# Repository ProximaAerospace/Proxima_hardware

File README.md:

# Proxima Hardware
Here you can find all CAD files for Proxima Official Flight Computers

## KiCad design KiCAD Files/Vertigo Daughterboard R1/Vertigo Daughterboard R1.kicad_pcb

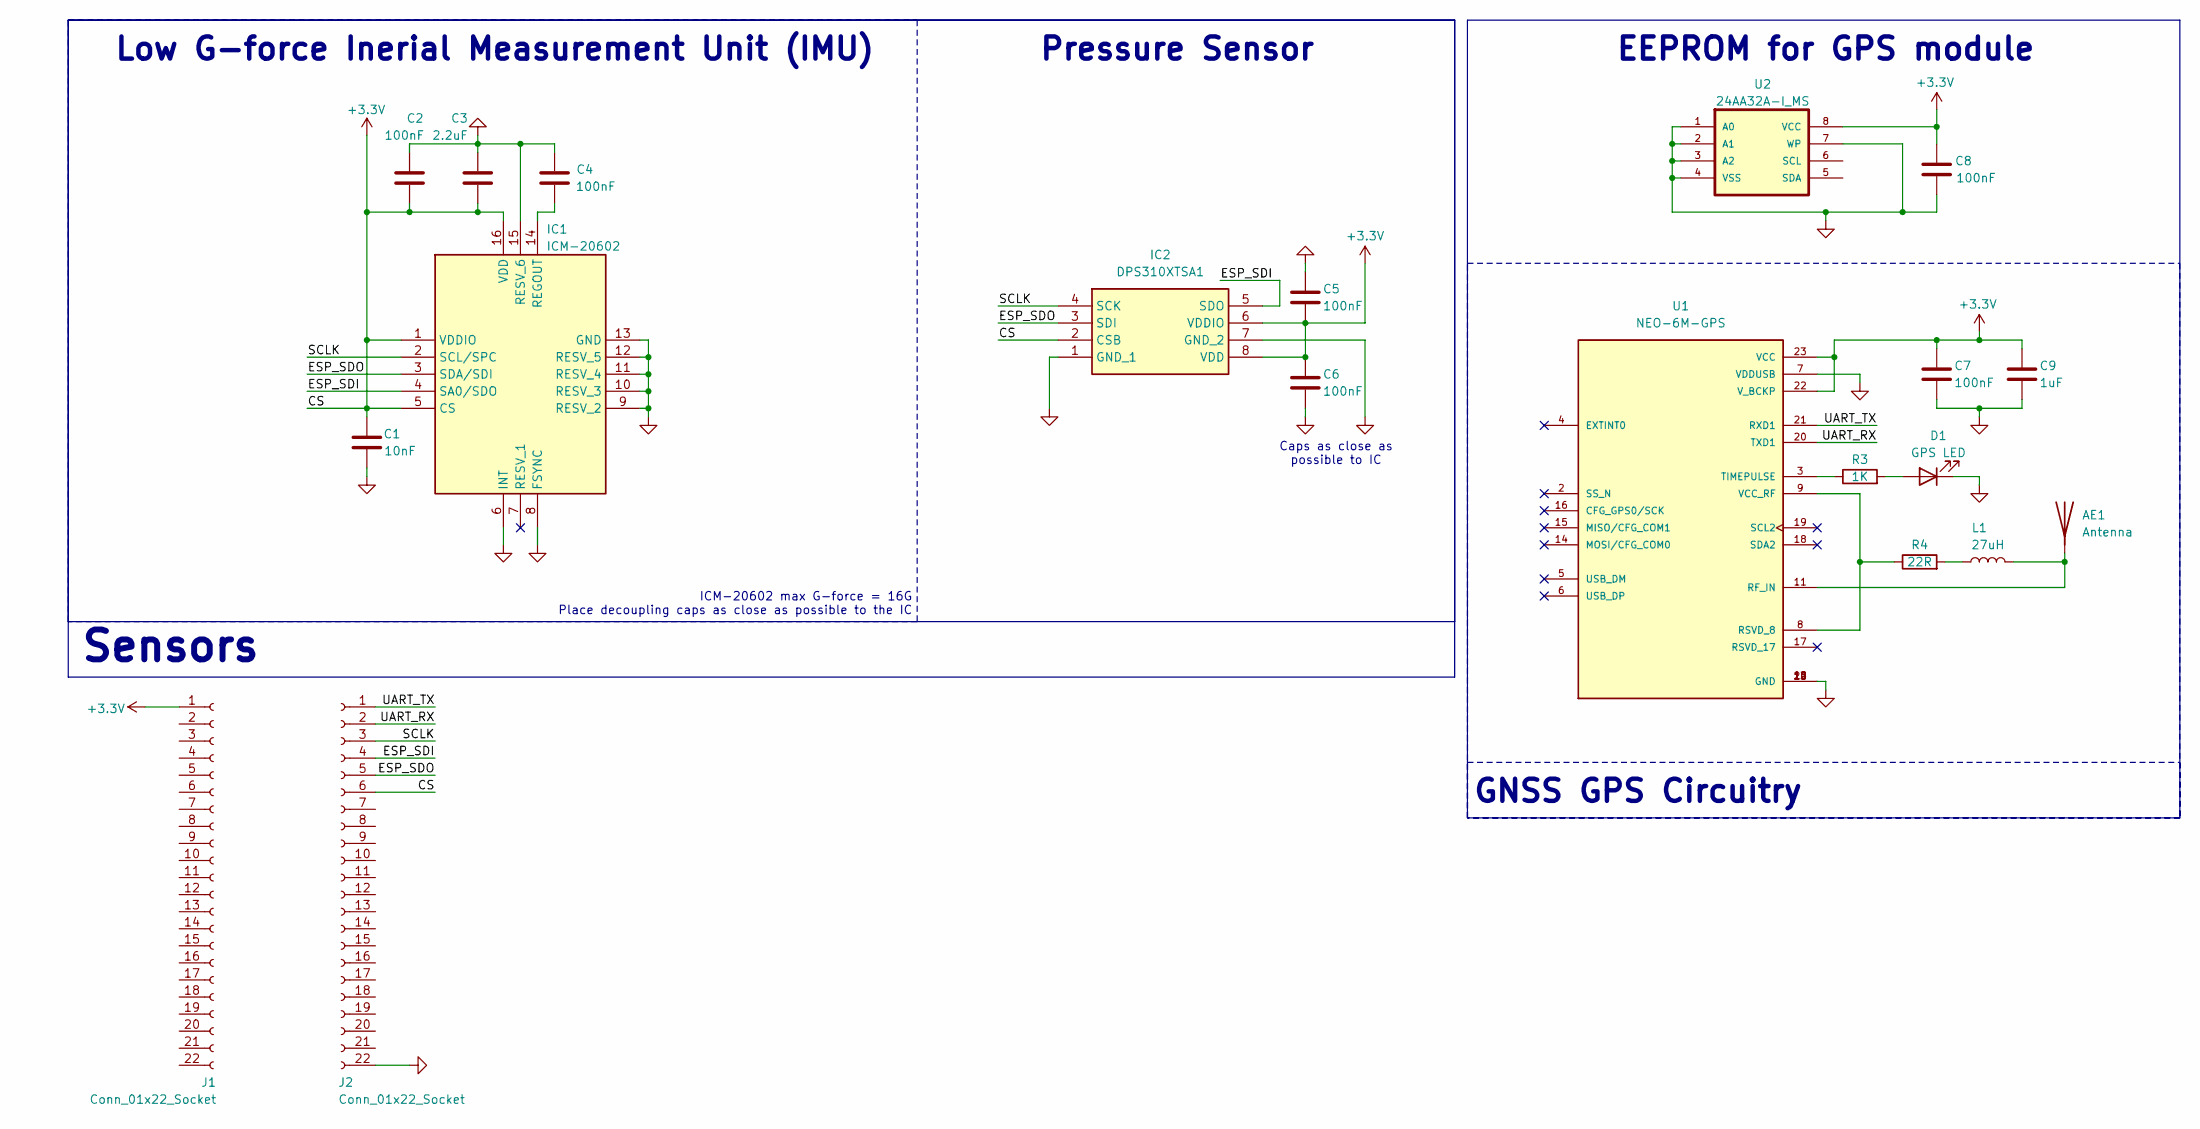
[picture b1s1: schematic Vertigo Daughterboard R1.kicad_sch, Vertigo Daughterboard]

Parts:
AE1: Antenna; U.FL_Hirose_U.FL-R-SMT-1_Vertical
C1: 10nF; C_0603_1608Metric
C2, C4, C5, C6, C7, C8: 100nF; C_0603_1608Metric
C3: 2.2uF; C_0603_1608Metric
C9: 1uF; C_0603_1608Metric
D1: GPS LED; LED_0603_1608Metric_Pad1.05x0.95mm_HandSolder
IC1: ICM-20602; PQFN50P300X300X80-16N; Manufacturer_Part_Number ICM-20602; Mouser Part Number 410-ICM-20602
IC2: DPS310XTSA1; Manufacturer_Part_Number DPS310XTSA1; Mouser Part Number 726-DPS310XTSA1
J1, J2: Conn_01x22_Socket; PinHeader_1x22_P2.54mm_Vertical
L1: 27uH; L_0402_1005Metric
R3: 1K; R_0805_2012Metric
R4: 22R; R_0402_1005Metric
U1: NEO-6M-GPS; XCVR_NEO-6M-GPS; PARTREV R15
U2: 24AA32A-I_MS; SOP65P490X110-8N

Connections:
+3.3V: C1.2, C2.2, C3.2, C5.2, C6.1, C7.1, C8.2, C9.1, IC1.1 (VDDIO), IC1.5 (CS), IC1.16 (VDD), IC2.2 (CSB), IC2.6 (VDDIO), IC2.8 (VDD), J1.1, J2.6, U1.22 (V_BCKP), U1.23 (VCC), U2.8 (VCC)
/ESP_SDI: IC1.4 (SA0/SDO), IC2.5 (SDO), J2.4
/ESP_SDO: IC1.3 (SDA/SDI), IC2.3 (SDI), J2.5
/SCLK: IC1.2 (SCL/SPC), IC2.4 (SCK), J2.3
/UART_RX: J2.2, U1.20 (TXD1)
/UART_TX: J2.1, U1.21 (RXD1)
GND: C1.1, C2.1, C3.1, C4.2, C5.1, C6.2, C7.2, C8.1, C9.2, D1.1 (K), IC1.6 (INT), IC1.8 (FSYNC), IC1.9 (RESV_2), IC1.10 (RESV_3), IC1.11 (RESV_4), IC1.12 (RESV_5), IC1.13 (GND), IC1.15 (RESV_6), IC2.1 (GND_1), IC2.7 (GND_2), J2.22, U1.7 (VDDUSB), U1.10 (GND), U1.12 (GND), U1.13 (GND), U1.24 (GND), U2.1 (A0), U2.2 (A1), U2.3 (A2), U2.4 (VSS), U2.7 (WP)
unnamed: AE1.1 (A), L1.2, U1.11 (RF_IN)
unnamed: D1.2 (A), R3.2
unnamed: C4.1, IC1.14 (REGOUT)
unnamed: L1.1, R4.2
unnamed: R4.1, U1.8 (RSVD_8), U1.9 (VCC_RF)
unnamed: R3.1, U1.3 (TIMEPULSE)

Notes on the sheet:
Caps as close as possible to IC
EEPROM for GPS module
GNSS GPS Circuitry
Sensors
ICM-20602 max G-force = 16G Place decoupling caps as close as possible to the IC
Low G-force Inerial Measurement Unit (IMU)
Pressure Sensor

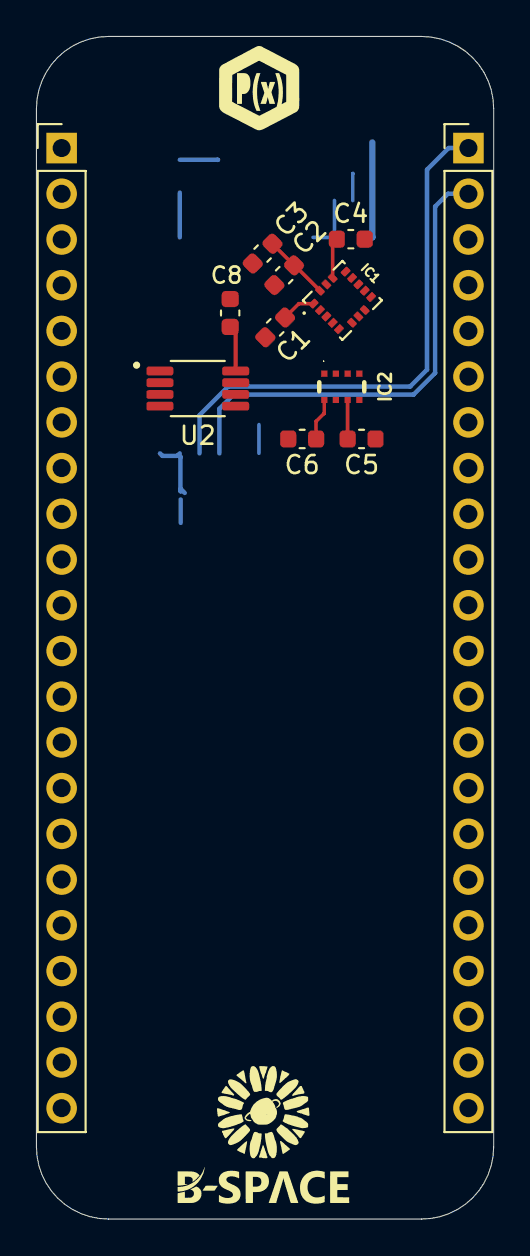
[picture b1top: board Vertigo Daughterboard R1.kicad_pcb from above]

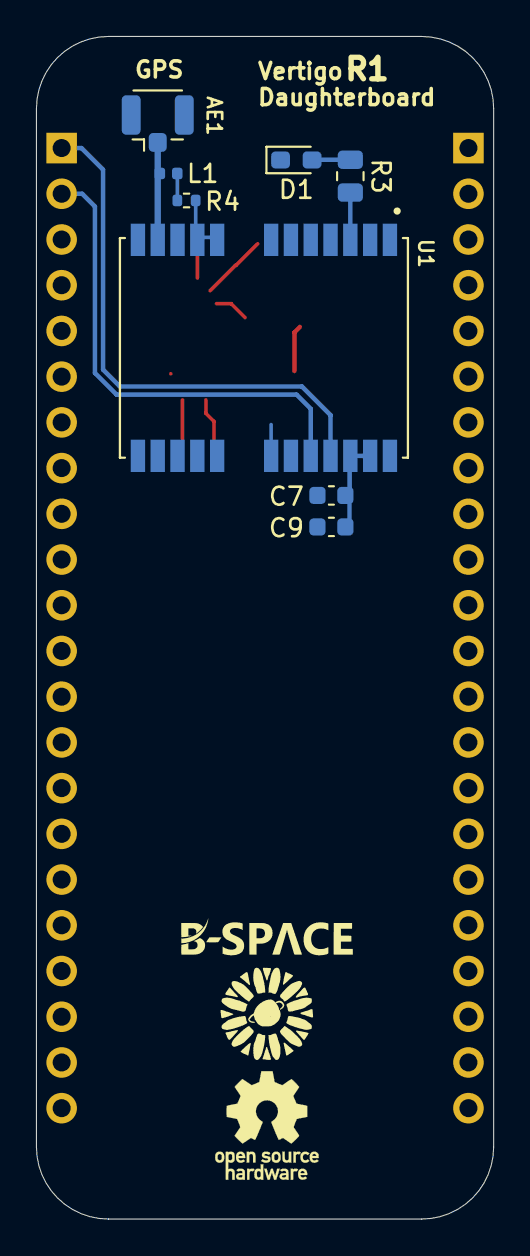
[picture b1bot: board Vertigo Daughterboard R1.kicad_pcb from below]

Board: 4 copper layers, 25.4 x 65.7 mm, 20 parts (8 on the bottom side), 13 nets.

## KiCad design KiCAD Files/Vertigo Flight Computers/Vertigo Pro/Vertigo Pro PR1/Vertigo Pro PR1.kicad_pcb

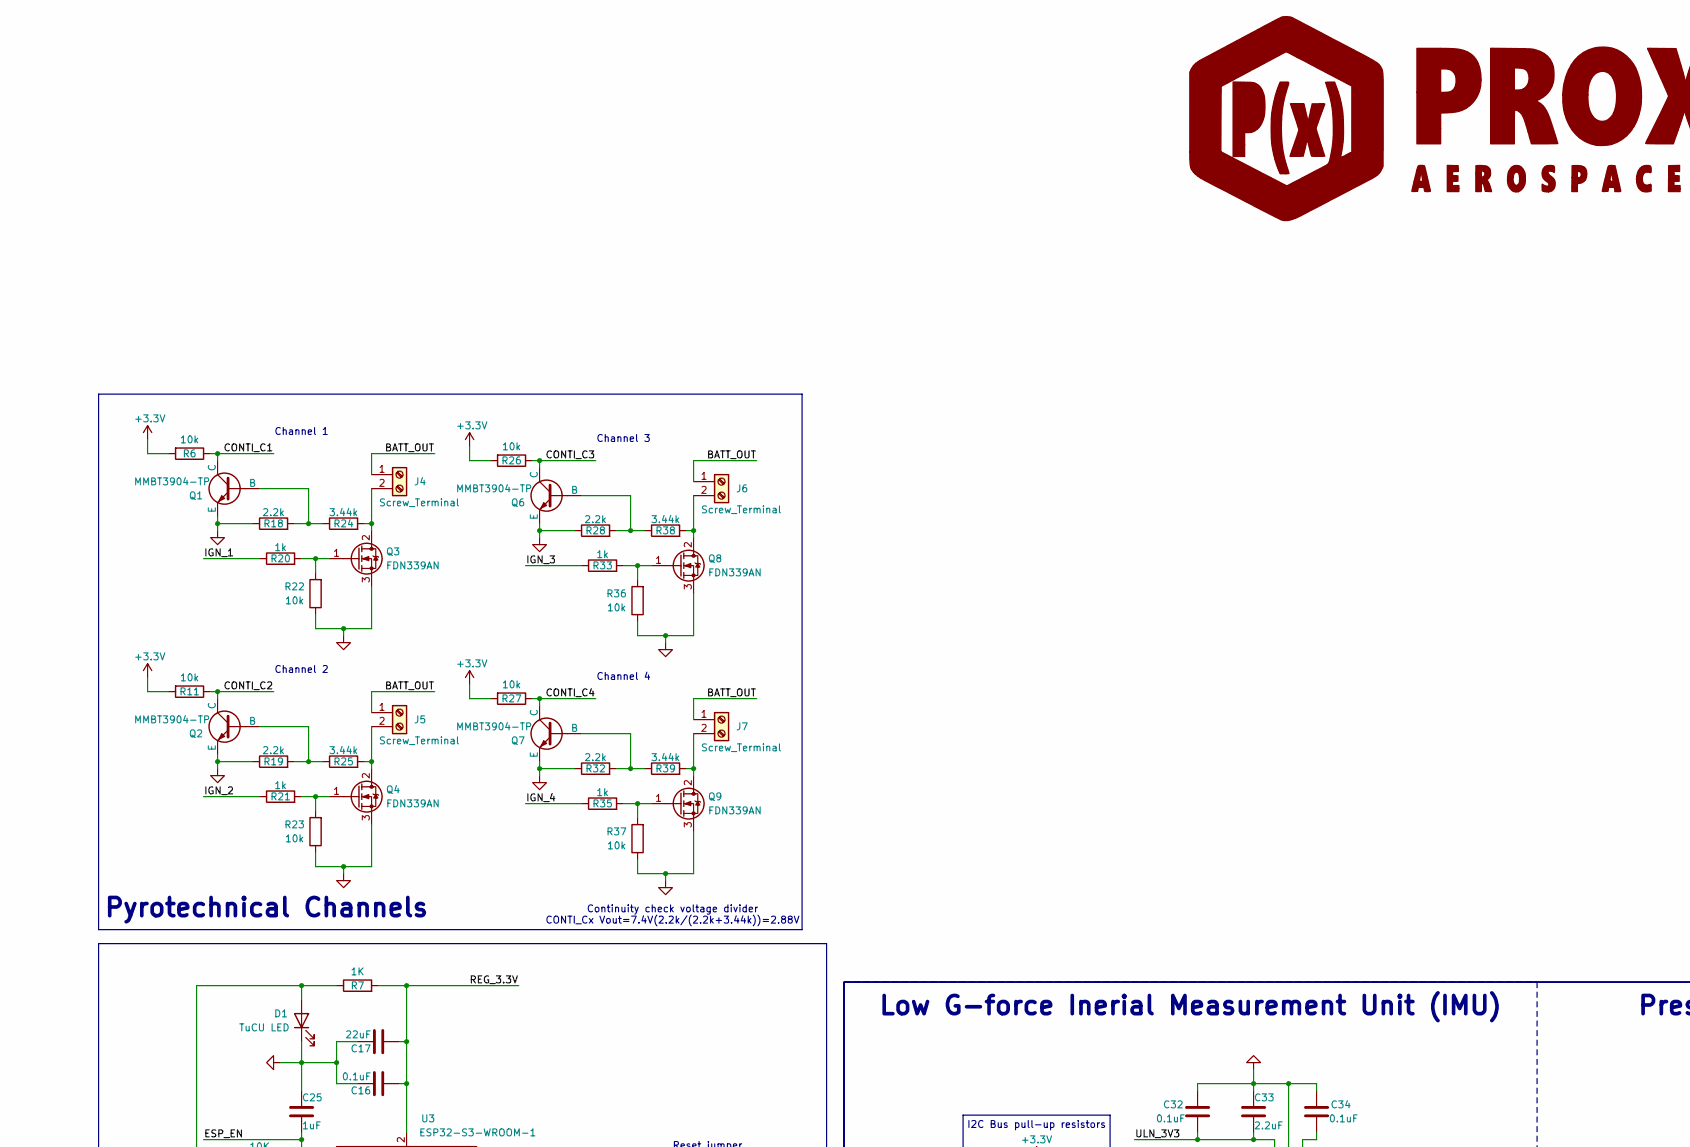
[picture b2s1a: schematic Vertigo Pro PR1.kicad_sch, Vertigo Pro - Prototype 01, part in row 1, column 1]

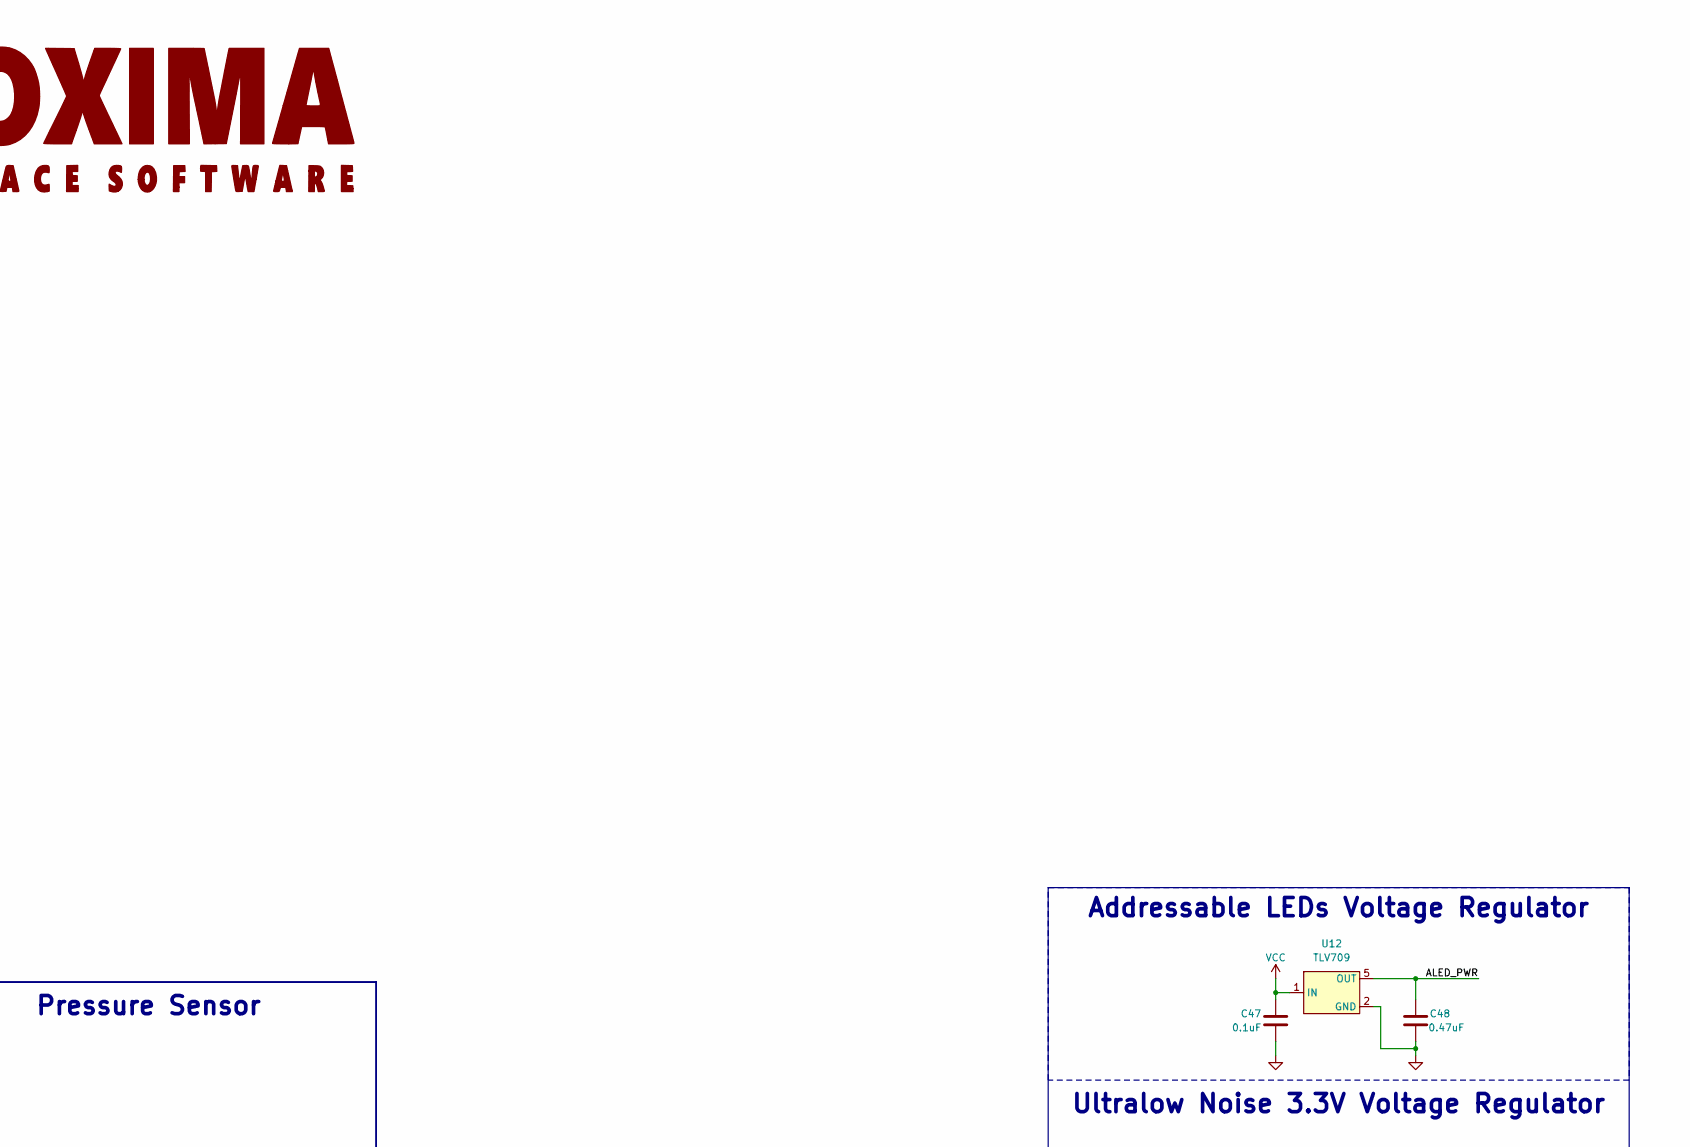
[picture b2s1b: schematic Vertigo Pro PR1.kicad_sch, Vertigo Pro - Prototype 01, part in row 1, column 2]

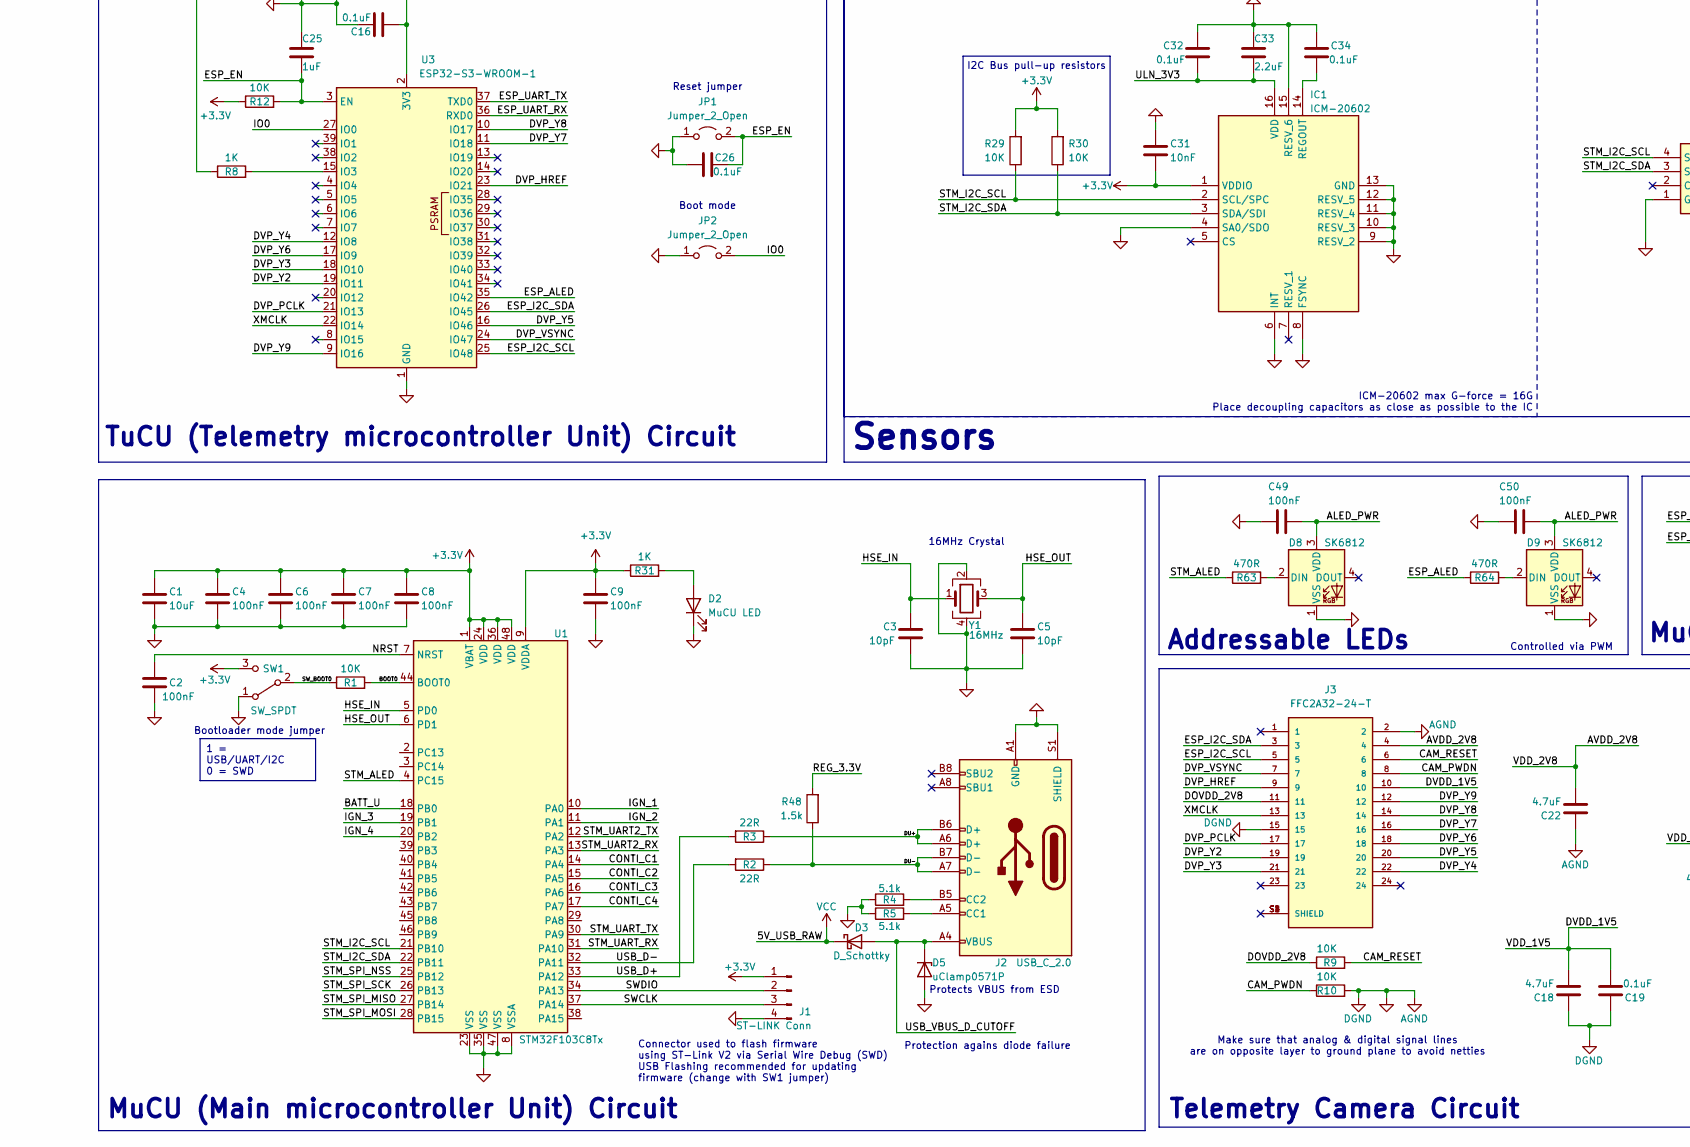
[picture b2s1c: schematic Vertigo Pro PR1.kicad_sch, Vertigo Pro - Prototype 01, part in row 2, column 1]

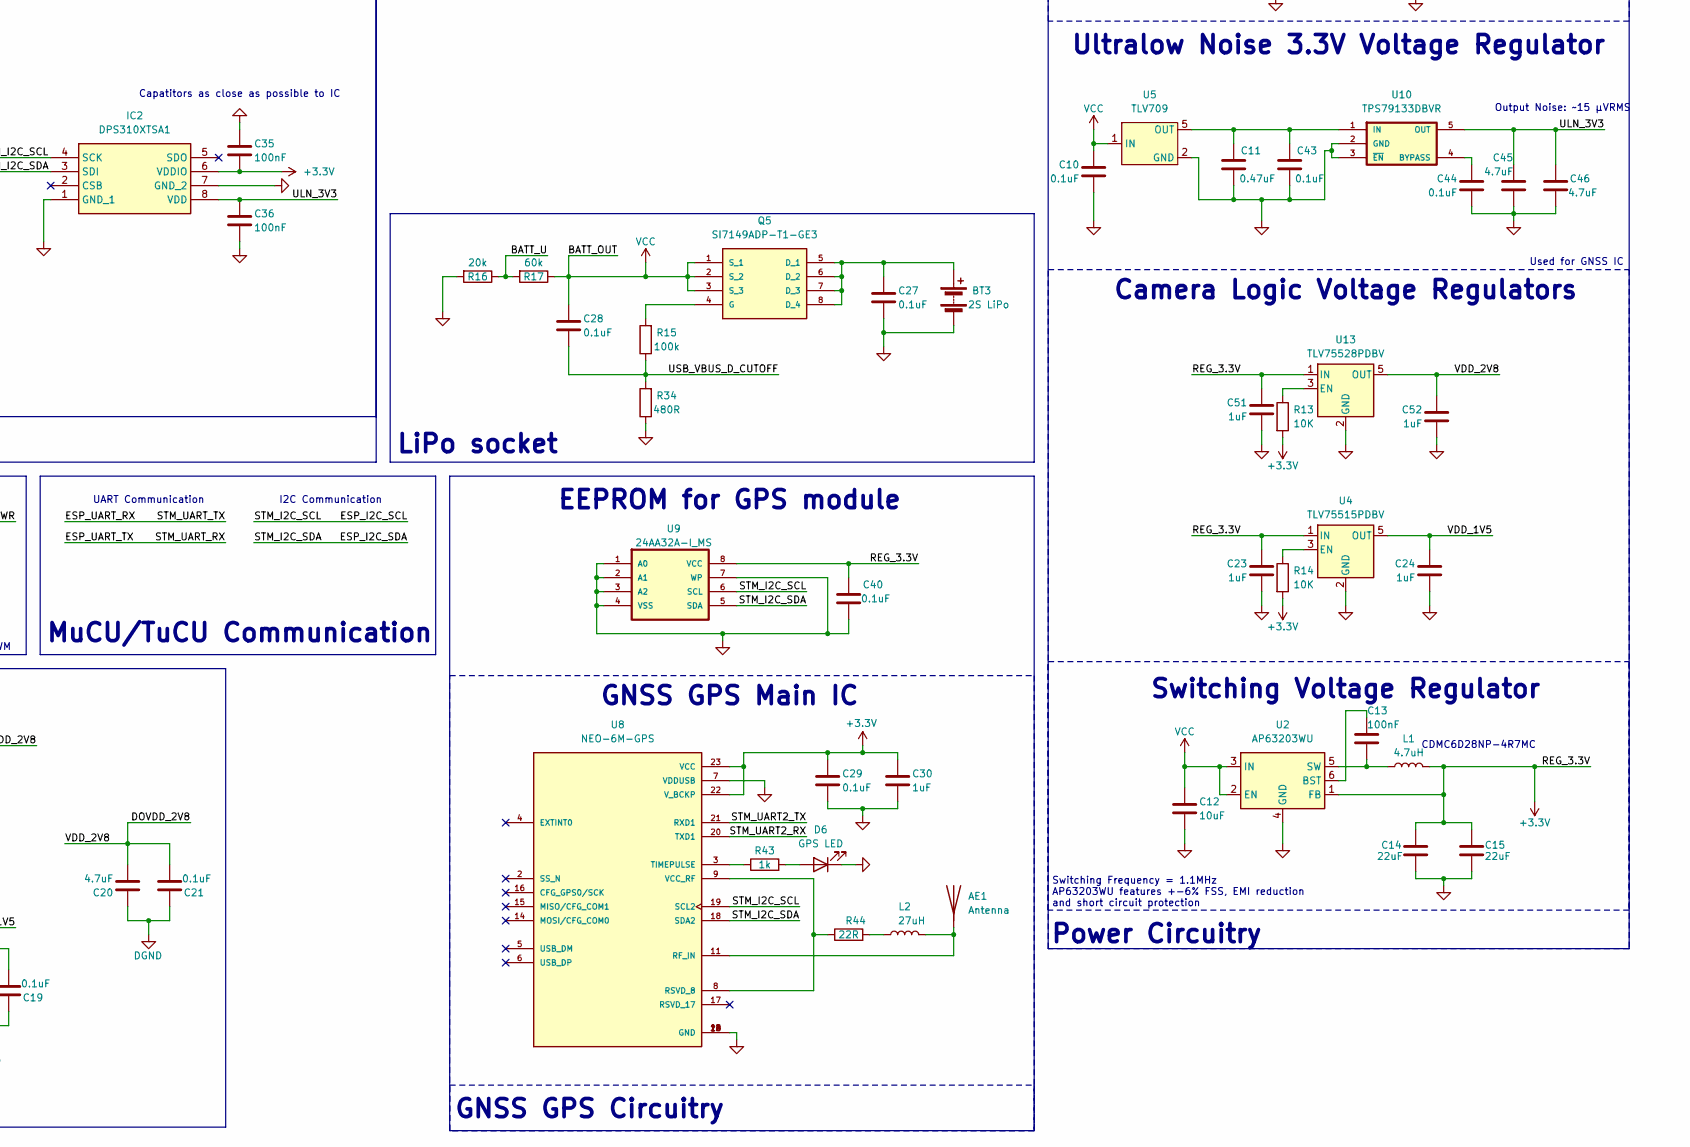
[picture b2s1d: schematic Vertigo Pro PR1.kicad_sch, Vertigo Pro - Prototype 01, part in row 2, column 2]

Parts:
AE1: Antenna; U.FL_Hirose_U.FL-R-SMT-1_Vertical
BT3: 2S LiPo; AMASS_XT30PW-F_1x02_P2.50mm_Horizontal
C1: 10uF; C_0603_1608Metric
C2, C4, C6, C7, C8, C9, C35, C36, C49, C50: 100nF; C_0603_1608Metric
C3, C5: 10pF; C_0603_1608Metric
C10, C16, C19, C21, C26, C32, C34, C40, C43, C44, C47: 0.1uF; C_0603_1608Metric
C11, C48: 0.47uF; C_0603_1608Metric
C12: 10uF; C_0603_1608Metric_Pad1.08x0.95mm_HandSolder
C13: 100nF; C_0603_1608Metric_Pad1.08x0.95mm_HandSolder
C14, C15, C17: 22uF; C_0603_1608Metric_Pad1.08x0.95mm_HandSolder
C18, C20, C45, C46: 4.7uF; C_0603_1608Metric_Pad1.08x0.95mm_HandSolder
C22: 4.7uF; C_0603_1608Metric
C23, C24, C25, C30, C51, C52: 1uF; C_0603_1608Metric_Pad1.08x0.95mm_HandSolder
C27, C28, C29: 0.1uF; C_0603_1608Metric_Pad1.08x0.95mm_HandSolder
C31: 10nF; C_0603_1608Metric
C33: 2.2uF; C_0603_1608Metric_Pad1.08x0.95mm_HandSolder
D1: TuCU LED; LED_0603_1608Metric_Pad1.05x0.95mm_HandSolder
D2: MuCU LED; LED_0603_1608Metric_Pad1.05x0.95mm_HandSolder
D3: D_Schottky; D_0603_1608Metric_Pad1.05x0.95mm_HandSolder
D5: uClamp0571P; Nexperia_DSN1608-2_1.6x0.8mm
D6: GPS LED; LED_0603_1608Metric_Pad1.05x0.95mm_HandSolder
D8, D9: SK6812; LED_SK6812_PLCC4_5.0x5.0mm_P3.2mm
IC1: ICM-20602; PQFN50P300X300X80-16N; Manufacturer_Part_Number ICM-20602; Mouser Part Number 410-ICM-20602
IC2: DPS310XTSA1; Manufacturer_Part_Number DPS310XTSA1; Mouser Part Number 726-DPS310XTSA1
J1: ST-LINK Conn; PinSocket_1x04_P1.27mm_Vertical
J2: USB_C_2.0; USB_C_Receptacle_HRO_TYPE-C-31-M-12
J3: FFC2A32-24-T; GCT_FFC2A32-24-T; PARTREV 0.1
J4, J5, J6, J7: Screw_Terminal; TerminalBlock_4Ucon_1x02_P3.50mm_Horizontal
JP1, JP2: Jumper_2_Open; SolderJumper-2_P1.3mm_Open_TrianglePad1.0x1.5mm
L1: 4.7uH; CDMC6D28NP-4R7MC
L2: 27uH; L_0402_1005Metric
Q1, Q2, Q6, Q7: MMBT3904-TP; SOT-23
Q3, Q4, Q8, Q9: FDN339AN; SOT-23
Q5: SI7149ADP-T1-GE3; POWERPAKSO-8; MOUSER_PART_NUMBER 78-SI7149ADP-T1-GE3
R1: 10K; R_0603_1608Metric
R2, R3: 22R; R_0603_1608Metric
R4, R5: 5.1k; R_0805_2012Metric_Pad1.20x1.40mm_HandSolder
R6, R11, R22, R23, R26, R27, R36, R37: 10k; R_0805_2012Metric_Pad1.20x1.40mm_HandSolder
R7, R8, R31: 1K; R_0805_2012Metric_Pad1.20x1.40mm_HandSolder
R9, R10, R12, R13, R14, R29, R30: 10K; R_0805_2012Metric_Pad1.20x1.40mm_HandSolder
R15: 100k; R_0805_2012Metric_Pad1.20x1.40mm_HandSolder
R16: 20k; R_0805_2012Metric_Pad1.20x1.40mm_HandSolder
R17: 60k; R_0805_2012Metric_Pad1.20x1.40mm_HandSolder
R18, R19, R28, R32: 2.2k; R_0805_2012Metric_Pad1.20x1.40mm_HandSolder
R20, R21, R33, R35, R43: 1k; R_0805_2012Metric_Pad1.20x1.40mm_HandSolder
R24, R25, R38, R39: 3.44k; R_0805_2012Metric_Pad1.20x1.40mm_HandSolder
R34: 480R; R_0805_2012Metric_Pad1.20x1.40mm_HandSolder
R44: 22R; R_0402_1005Metric
R48: 1.5k; R_0603_1608Metric
R63, R64: 470R; R_1206_3216Metric
SW1: SW_SPDT; SolderJumper-3_P2.0mm_Open_TrianglePad1.0x1.5mm_NumberLabels
U1: STM32F103C8Tx; LQFP-48_7x7mm_P0.5mm
U2: AP63203WU; TSOT-23-6
U3: ESP32-S3-WROOM-1
U4: TLV75515PDBV; SOT-23-5
U5, U12: TLV709; SOT95P280X145-5N
U8: NEO-6M-GPS; XCVR_NEO-6M-GPS; PARTREV R15
U9: 24AA32A-I_MS; SOP65P490X110-8N
U10: TPS79133DBVR; SOT95P280X145-5N
U13: TLV75528PDBV; SOT-23-5
Y1: 16MHz; XTAL_TSX-3225_16.0000MF09Z-AC6

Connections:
+3.3V: C1.1, C4.1, C6.1, C7.1, C8.1, C9.1, C14.1, C15.1, C16.2, C17.2, C23.2, C29.1, C30.1, C31.2, C35.2, C40.2, C51.2, IC1.1 (VDDIO), IC2.6 (VDDIO), J1.1, L1.2, R6.2, R7.2, R11.2, R12.1, R13.2, R14.2, R26.2, R27.2, R29.2, R30.2, R31.1, R48.2, SW1.3 (C), U1.1 (VBAT), U1.9 (VDDA), U1.24 (VDD), U1.36 (VDD), U1.48 (VDD), U2.1 (FB), U3.2 (3V3), U4.1 (IN), U8.22 (V_BCKP), U8.23 (VCC), U9.8 (VCC), U13.1 (IN); also elsewhere on the board
/ALED_PWR: C48.2, C49.1, C50.1, D8.3 (VDD), D9.3 (VDD), U12.5 (OUT)
/AVDD_2V8: C20.2, C21.2, C22.2, C52.2, J3.4, J3.11, R9.1, U13.5 (OUT)
/BATT_U: R16.1, R17.2, U1.18 (PB0)
/BOOT0: R1.2, U1.44 (BOOT0)
/CAM_PWDN: J3.8, R10.1
/CAM_RESET: J3.6, R9.2
/CONTI_C1: Q1.1 (C), R6.1, U1.14 (PA4)
/CONTI_C2: Q2.1 (C), R11.1, U1.15 (PA5)
/CONTI_C3: Q6.1 (C), R26.1, U1.16 (PA6)
/CONTI_C4: Q7.1 (C), R27.1, U1.17 (PA7)
/DU+: J2.A6 (D+), J2.B6 (D+), R3.1
/DU-: J2.A7 (D-), J2.B7 (D-), R2.1, R48.1
/DVDD_1V5: C18.2, C19.2, C24.2, J3.10, U4.5 (OUT)
/DVP_HREF: J3.9, U3.23 (IO21)
/DVP_PCLK: J3.17, U3.21 (IO13)
/DVP_VSYNC: J3.7, U3.24 (IO47)
/DVP_Y2: J3.19, U3.19 (IO11)
/DVP_Y3: J3.21, U3.18 (IO10)
/DVP_Y4: J3.22, U3.12 (IO8)
/DVP_Y5: J3.20, U3.16 (IO46)
/DVP_Y6: J3.18, U3.17 (IO9)
/DVP_Y7: J3.16, U3.11 (IO18)
/DVP_Y8: J3.14, U3.10 (IO17)
/DVP_Y9: J3.12, U3.9 (IO16)
/ESP_ALED: R64.1, U3.35 (IO42)
/ESP_EN: C25.2, C26.2, JP1.2 (B), R12.2, U3.3 (EN)
/ESP_I2C_SCL: IC1.2 (SCL/SPC), IC2.4 (SCK), J3.5, R29.1, U1.21 (PB10), U3.25 (IO48), U8.19 (SCL2), U9.6 (SCL); also elsewhere on the board
/ESP_I2C_SDA: IC1.3 (SDA/SDI), IC2.3 (SDI), J3.3, R30.1, U1.22 (PB11), U3.26 (IO45), U8.18 (SDA2), U9.5 (SDA); also elsewhere on the board
/ESP_UART_RX: U1.30 (PA9), U3.36 (RXD0); also elsewhere on the board
/ESP_UART_TX: U1.31 (PA10), U3.37 (TXD0); also elsewhere on the board
/HSE_IN: C3.1, U1.5 (PD0), Y1.1
/HSE_OUT: C5.1, U1.6 (PD1), Y1.3
/IGN_1: R20.1, U1.10 (PA0)
/IGN_2: R21.1, U1.11 (PA1)
/IGN_3: R33.1, U1.19 (PB1)
/IGN_4: R35.1, U1.20 (PB2)
/IO0: JP2.2 (B), U3.27 (IO0)
/NRST: C2.1, U1.7 (NRST)
/STM_ALED: R63.1, U1.4 (PC15)
/STM_SPI_MISO: U1.27 (PB14); also elsewhere on the board
/STM_SPI_MOSI: U1.28 (PB15); also elsewhere on the board
/STM_SPI_NSS: U1.25 (PB12); also elsewhere on the board
/STM_SPI_SCK: U1.26 (PB13); also elsewhere on the board
/STM_UART2_RX: U1.13 (PA3), U8.20 (TXD1); also elsewhere on the board
/STM_UART2_TX: U1.12 (PA2), U8.21 (RXD1); also elsewhere on the board
/SWCLK: J1.3, U1.37 (PA14)
/SWDIO: J1.2, U1.34 (PA13)
/SW_BOOT0: R1.1, SW1.2 (B)
/ULN_3V3: C32.2, C33.2, C36.1, C45.2, C46.2, IC1.16 (VDD), IC2.8 (VDD), U10.5 (OUT)
/USB_D+: R3.2, U1.33 (PA12)
/USB_D-: R2.2, U1.32 (PA11)
/USB_VBUS_D_CUTOFF: C28.2, D3.2 (A), D5.1 (K), J2.A4 (VBUS), J2.A9 (VBUS), J2.B4 (VBUS), J2.B9 (VBUS), R15.1, R34.2
/XMCLK: J3.13, U3.22 (IO14)
AGND: BT3.2 (-), C1.2, C2.2, C3.2, C4.2, C5.2, C6.2, C7.2, C8.2, C9.2, C10.1, C11.1, C12.2, C14.2, C15.2, C16.1, C17.1, C18.1, C19.1, C20.1, C21.1, C22.1, C23.1, C24.1, C25.1, C26.1, C27.2, C29.2, C30.2, C31.1, C32.1, C33.1, C34.2, C35.1, C36.2, C40.1, C43.1, C44.1, C45.1, C46.1, C47.1, C48.1, C49.2, C50.2, C51.1, C52.1, D1.1 (K), D2.1 (K), D5.2 (A), D6.1 (K), D8.1 (VSS), D9.1 (VSS), IC1.4 (SA0/SDO), IC1.6 (INT), IC1.8 (FSYNC), IC1.9 (RESV_2), IC1.10 (RESV_3), IC1.11 (RESV_4), IC1.12 (RESV_5), IC1.13 (GND), IC1.15 (RESV_6), IC2.1 (GND_1), IC2.7 (GND_2), J1.4, J2.A1 (GND), J2.A12 (GND), J2.B1 (GND), J2.B12 (GND), J2.S1 (SHIELD), J3.2, J3.15, JP1.1 (A), JP2.1 (A), Q1.3 (E), Q2.3 (E), Q3.3 (S), Q4.3 (S), Q6.3 (E), Q7.3 (E), Q8.3 (S), Q9.3 (S), R4.1, R5.1, R10.2, R16.2, R18.1, R19.1, R22.1, R23.1, R28.1, R32.1, R34.1, R36.1, R37.1, SW1.1 (A), U1.8 (VSSA), U1.23 (VSS), U1.35 (VSS), U1.47 (VSS), U2.4 (GND), U3.1 (GND), U3.40 (GND), U3.41 (GND), U4.2 (GND), U5.2 (GND), U8.7 (VDDUSB), U8.10 (GND), U8.12 (GND), U8.13 (GND), U8.24 (GND), U9.1 (A0), U9.2 (A1), U9.3 (A2), U9.4 (VSS), U9.7 (WP), U10.2 (GND), U10.3 (~EN), U12.2 (GND), U13.2 (GND), Y1.2, Y1.4; also elsewhere on the board
unnamed: AE1.1 (A), L2.2, U8.11 (RF_IN)
unnamed: BT3.1 (+), C27.1, Q5.5 (D_1), Q5.6 (D_2), Q5.7 (D_3), Q5.8 (D_4)
unnamed: D1.2 (A), R7.1, R8.1
unnamed: D2.2 (A), R31.2
unnamed: D6.2 (A), R43.2
unnamed: D8.2 (DIN), R63.2
unnamed 61: D9.2 (DIN), R64.2; also elsewhere on the board
unnamed: C34.1, IC1.14 (REGOUT)
unnamed: J2.A5 (CC1), R5.2
unnamed: J2.B5 (CC2), R4.2
unnamed: J4.2, Q3.2 (D), R24.2
unnamed: J5.2, Q4.2 (D), R25.2
unnamed: J6.2, Q8.2 (D), R38.2
unnamed: J7.2, Q9.2 (D), R39.2
unnamed: L2.1, R44.2
unnamed: Q1.2 (B), R18.2, R24.1
unnamed: Q2.2 (B), R19.2, R25.1
unnamed: Q3.1 (G), R20.2, R22.2
unnamed: Q4.1 (G), R21.2, R23.2
unnamed: Q5.4 (G), R15.2
unnamed: Q6.2 (B), R28.2, R38.1
unnamed: Q7.2 (B), R32.2, R39.1
unnamed: Q8.1 (G), R33.2, R36.2
unnamed: Q9.1 (G), R35.2, R37.2
unnamed: C13.1, U2.6 (BST)
unnamed: C13.2, L1.1, U2.5 (SW)
unnamed: R8.2, U3.15 (IO3)
unnamed: R14.1, U4.3 (EN)
unnamed: R44.1, U8.8 (RSVD_8), U8.9 (VCC_RF)
unnamed: R43.1, U8.3 (TIMEPULSE)
unnamed: C44.2, U10.4 (BYPASS)
unnamed: C11.2, C43.2, U5.5 (OUT), U10.1 (IN)
unnamed: R13.1, U13.3 (EN)
VCC: C10.2, C12.1, C28.1, C47.2, D3.1 (K), J4.1, J5.1, J6.1, J7.1, Q5.1 (S_1), Q5.2 (S_2), Q5.3 (S_3), R17.1, U2.2 (EN), U2.3 (IN), U5.1 (IN), U12.1 (IN)

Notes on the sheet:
1 = USB/UART/I2C 0 = SWD
Switching Voltage Regulator
I2C Bus pull-up resistors
Switching Frequency = 1.1MHz AP63203WU features +-6% FSS, EMI reduction and short circuit protection
Sensors
GNSS GPS Main IC
GNSS GPS Circuitry
Camera Logic Voltage Regulators
Addressable LEDs Voltage Regulator
CDMC6D28NP-4R7MC
Connector used to flash firmware using ST-Link V2 via Serial Wire Debug (SWD) USB Flashing recommended for updating firmware (change with SW1 jumper)
MuCU (Main microcontroller Unit) Circuit
Channel 1
Capatitors as close as possible to IC
Addressable LEDs
Channel 4
Continuity check voltage divider CONTI_Cx Vout=7.4V(2.2k/(2.2k+3.44k))=2.88V
Used for GNSS IC
Protects VBUS from ESD
Ultralow Noise 3.3V Voltage Regulator
ICM-20602 max G-force = 16G Place decoupling capacitors as close as possible to the IC
Channel 2
Output Noise: ~15 μVRMS
MuCU/TuCU Communication
Pyrotechnical Channels
Make sure that analog & digital signal lines are on opposite layer to ground plane to avoid netties
Controlled via PWM
LiPo socket
Pressure Sensor
Telemetry Camera Circuit
EEPROM for GPS module
I2C Communication
Low G-force Inerial Measurement Unit (IMU)
UART Communication
Bootloader mode jumper
Reset jumper
Protection agains diode failure
16MHz Crystal
TuCU (Telemetry microcontroller Unit) Circuit
Power Circuitry

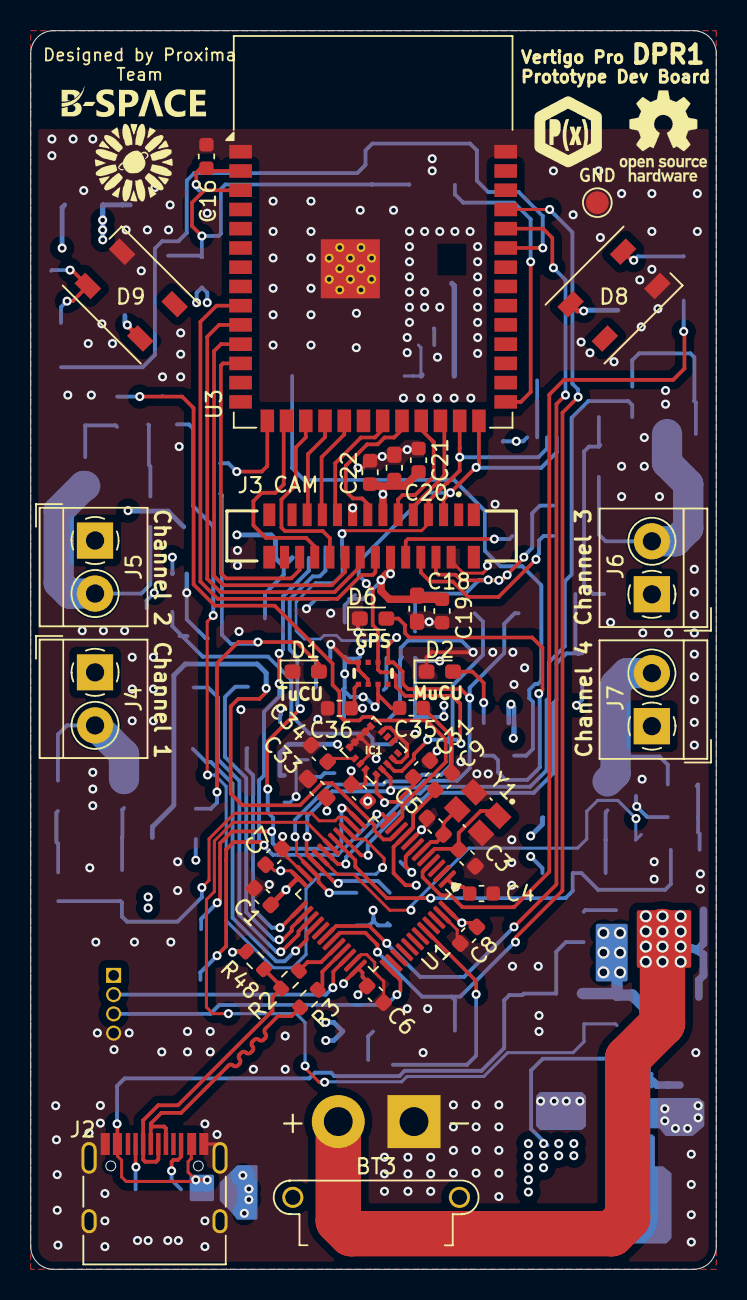
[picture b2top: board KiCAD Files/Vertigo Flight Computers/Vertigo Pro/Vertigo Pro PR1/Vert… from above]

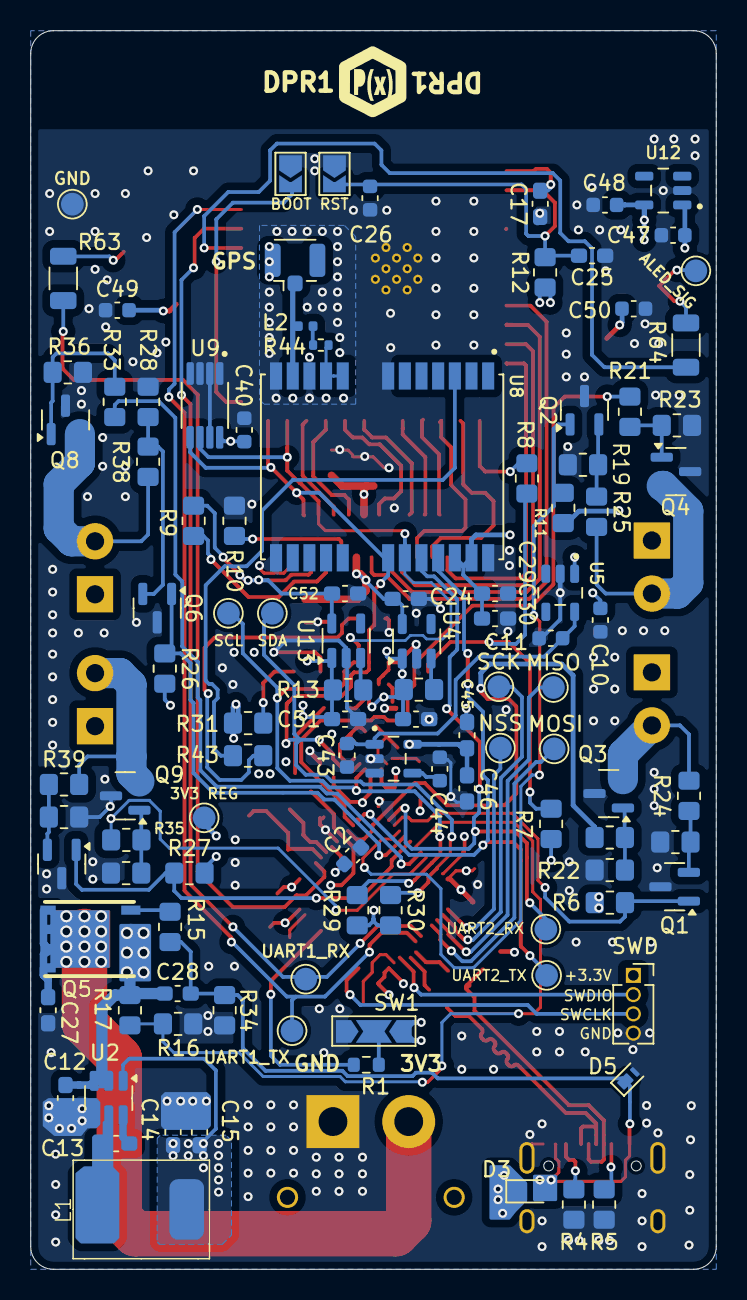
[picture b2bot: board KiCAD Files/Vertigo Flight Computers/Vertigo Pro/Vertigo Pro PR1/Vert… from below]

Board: 4 copper layers, 45.2 x 81.8 mm, 148 parts (107 on the bottom side), 89 nets.

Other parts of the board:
3V3 REG: TestPoint_Pad_D1.5mm
ALED_SIG: TestPoint_Pad_D1.5mm
GND: TestPoint_Pad_D1.5mm
GND#2: TestPoint_Pad_D1.5mm
MISO: TestPoint_Pad_D1.5mm
MOSI: TestPoint_Pad_D1.5mm
NSS: TestPoint_Pad_D1.5mm
SCK: TestPoint_Pad_D1.5mm
SCL: TestPoint_Pad_D1.5mm
SDA: TestPoint_Pad_D1.5mm
UART1_RX, UART1_TX, UART2_RX, UART2_TX: TestPoint_Pad_D1.5mm

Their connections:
+3.3V: 3V3 REG.1; also elsewhere on the board
/ESP_I2C_SCL: SCL.1; also elsewhere on the board
/ESP_I2C_SDA: SDA.1; also elsewhere on the board
/ESP_UART_RX: UART1_RX.1; also elsewhere on the board
/ESP_UART_TX: UART1_TX.1; also elsewhere on the board
/STM_SPI_MISO: MISO.1; also elsewhere on the board
/STM_SPI_MOSI: MOSI.1; also elsewhere on the board
/STM_SPI_NSS: NSS.1; also elsewhere on the board
/STM_SPI_SCK: SCK.1; also elsewhere on the board
/STM_UART2_RX: UART2_RX.1; also elsewhere on the board
/STM_UART2_TX: UART2_TX.1; also elsewhere on the board
AGND: GND.1, GND#2.1; also elsewhere on the board
unnamed 61: ALED_SIG.1; also elsewhere on the board
